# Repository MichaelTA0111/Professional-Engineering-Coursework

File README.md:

# Air Pollution Monitoring System
This is a repository for a free and open source air pollution monitoring system.

## Documentation
The documentation for this project is available in this repository as "APMS Documentation.pdf".

## Components
The system uses the following electronic components:
* Mbed NXP LPC1768
* Adafruit Monochrome 0.91” 128x32 I2C OLED Display
* RJ45 8-pin Connector
* SparkFun RJ45 Breakout
* RJ45 CAT6 Cable 5 m
* Adafruit BME680
* Thumb Joystick
* Thumb Joystick Breakout Board
* 5W Plug Adapter 5V DC
* DC Barrel Power Jack/Connector

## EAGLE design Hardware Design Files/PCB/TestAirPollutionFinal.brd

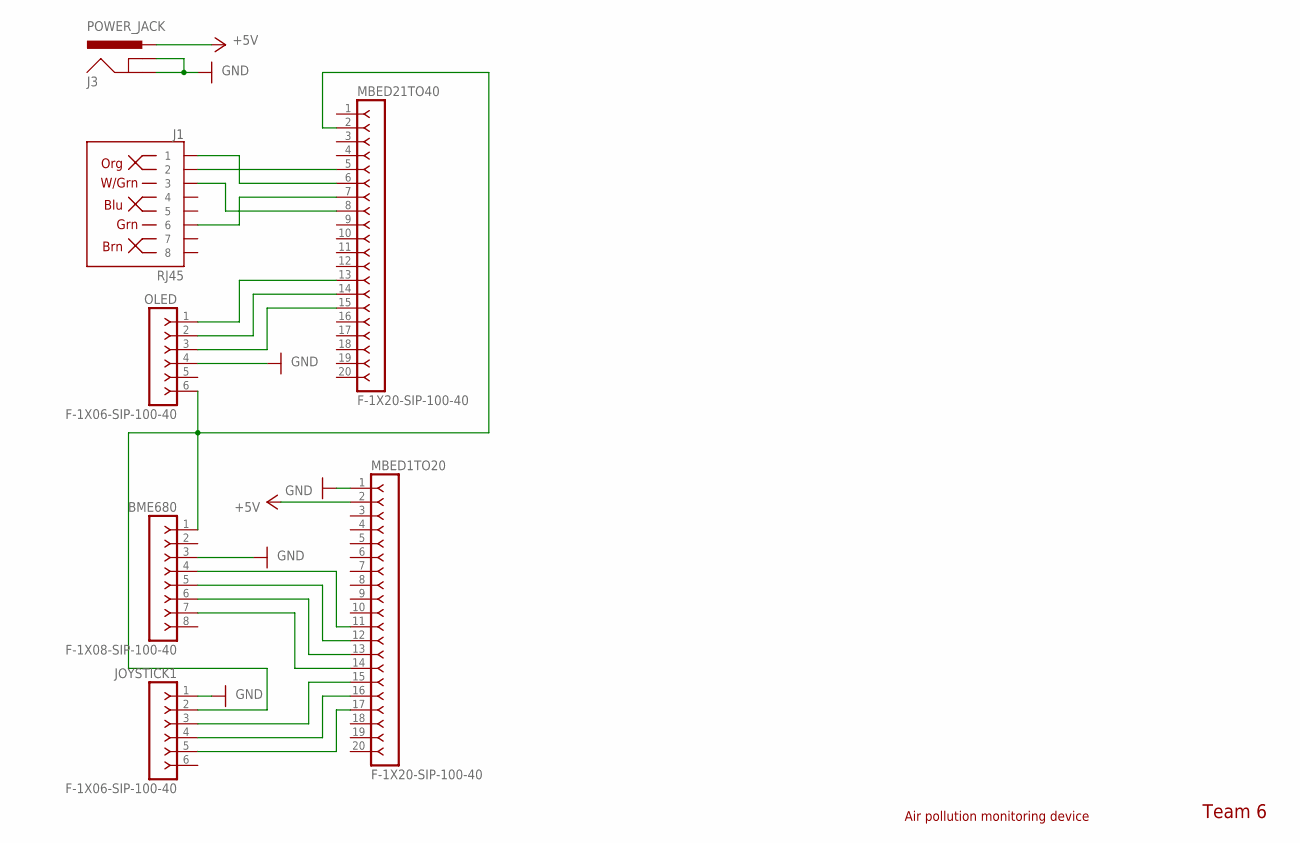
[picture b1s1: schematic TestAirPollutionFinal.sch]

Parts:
BME680: F-1X08-SIP-100-40; SIP-100-08-40
J1: RJ45; RJ45-8
J3: POWER_JACK; POWER_JACK_PTH
JOYSTICK1: F-1X06-SIP-100-40; SIP-100-06-40
MBED1TO20, MBED21TO40: F-1X20-SIP-100-40; SIP-100-20-40
OLED: F-1X06-SIP-100-40; SIP-100-06-40

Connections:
+5V: J3.PWR, MBED1TO20.2
CS: BME680.7, MBED1TO20.14
GND: BME680.3, J3.GND, J3.GNDBREAK, JOYSTICK1.1, MBED1TO20.1, OLED.4
RD+: J1.1, MBED21TO40.6
RD-: J1.2, MBED21TO40.5
RESET: MBED21TO40.15, OLED.3
SCK: BME680.4, MBED1TO20.11
SCLP27: MBED21TO40.14, OLED.2
SDAP28: MBED21TO40.13, OLED.1
SDI: BME680.6, MBED1TO20.13
SDO: BME680.5, MBED1TO20.12
SW: JOYSTICK1.5, MBED1TO20.17
TD+: J1.3, MBED21TO40.8
TD-: J1.6, MBED21TO40.7
VRX: JOYSTICK1.3, MBED1TO20.15
VRY: JOYSTICK1.4, MBED1TO20.16
VU: BME680.1, JOYSTICK1.2, MBED21TO40.2, OLED.6

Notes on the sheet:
Team 6
Air pollution monitoring device

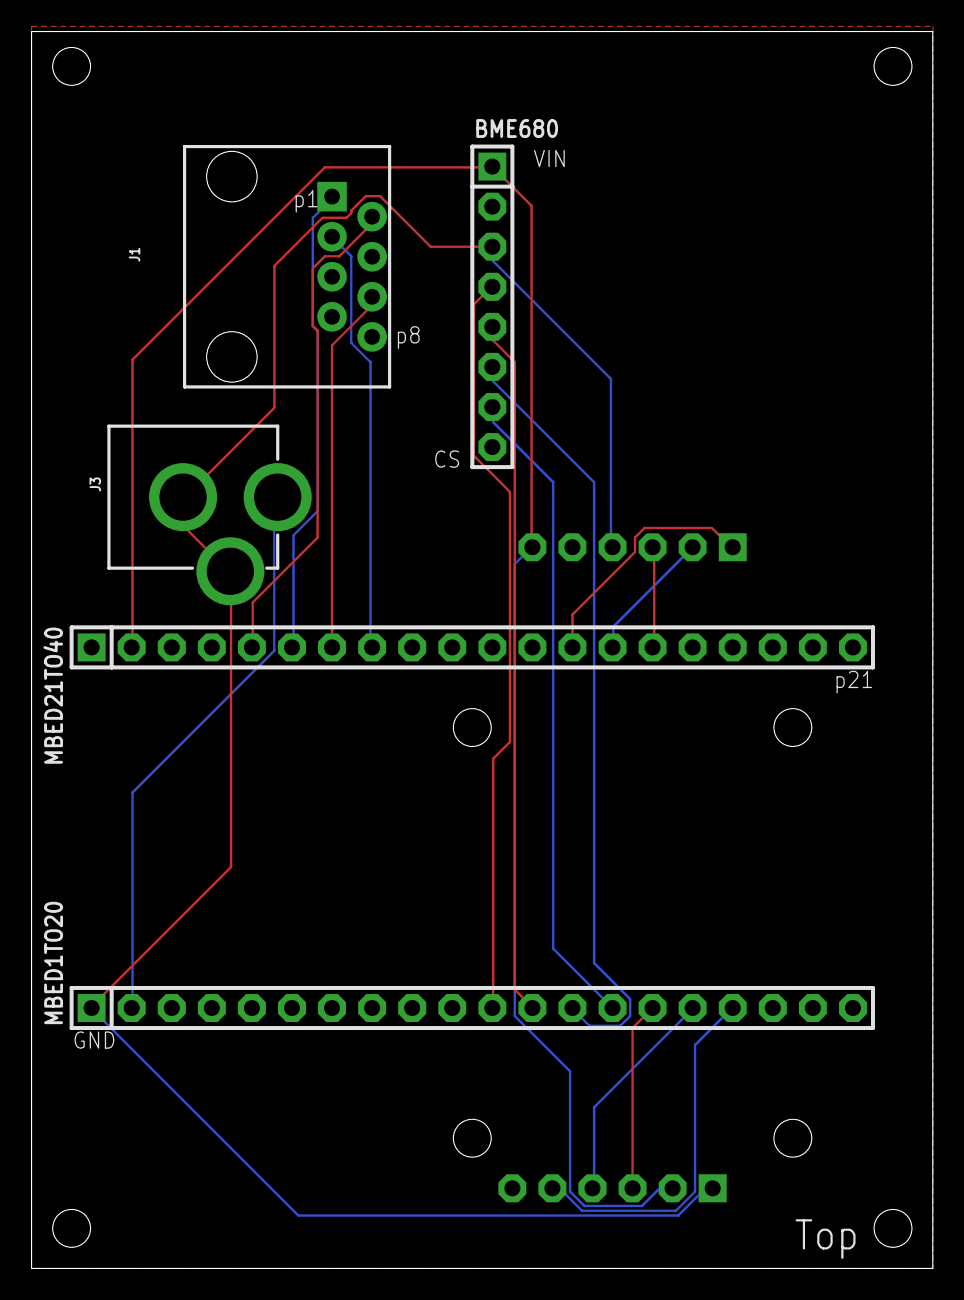
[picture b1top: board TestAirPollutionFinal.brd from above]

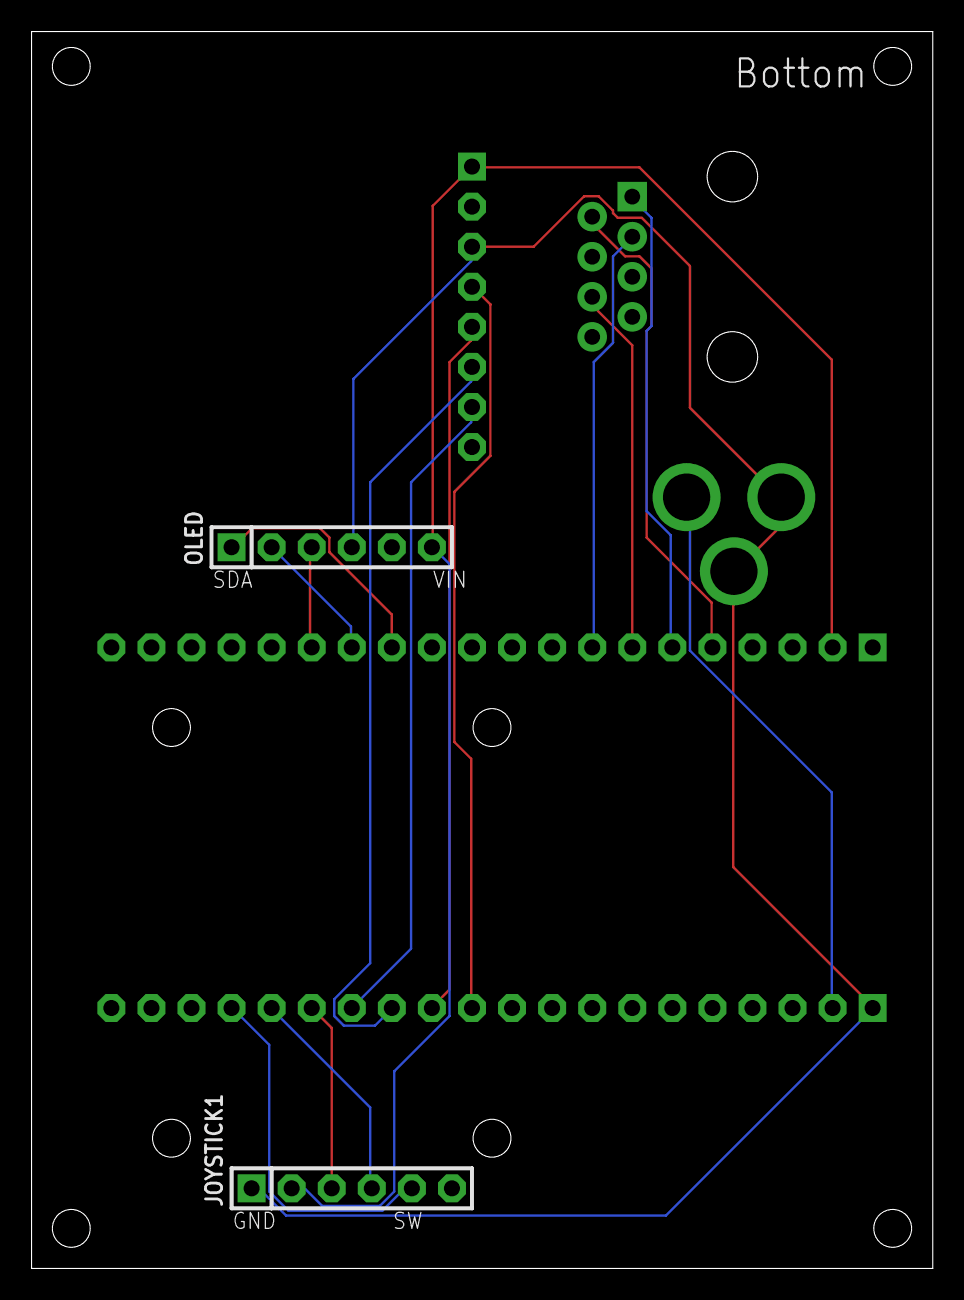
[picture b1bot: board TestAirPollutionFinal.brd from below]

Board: 2 copper layers, 57.1 x 78.4 mm, 7 parts (2 on the bottom side), 17 nets.

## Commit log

2021-01-21 Added link to attendance tracker
2021-01-22 Added CMake files to .gitignore
2021-01-22 Removed redundant definition
2021-01-23 Add mbed-os.lib
2021-01-23 Replace EventIntervalTrigger.h and EventIntervalTrigger.cpp with event-interval-trigger.lib
2021-01-27 Add LM75B.lib
2021-01-27 Correct comment in DatabaseManager.py
2021-02-02 Database can be read, graphs can be plotted
2021-02-06 Added statistics calculations to the data
2021-02-07 Fixed comments
2021-02-07 Added a method to convert a unix timestamp to a date string
2021-02-07 Added exporting data as a csv
2021-02-12 Slightly modified exporting to a csv to allow spaces in column headers
2021-02-12 Created a class for the sensors to inherit from
2021-02-12 Added watermarks to spite David Lim
2021-02-12 Added saving the graph to run.py
2021-02-13 Add default constructor to DataPackage.h and DataPackage.cpp
2021-02-13 Moved code from DataPackage.h to DataPackage.cpp
2021-02-15 Add PCB design files
2021-02-16 Redone comments
2021-02-16 Added a static method to parse a vector of data packets as a JSON
2021-02-16 Revert "Added a static method to parse a vector of data packets as a JSON"
    This reverts commit 7852cdb8
2021-02-16 Fixed spelling error in DataPackage.h
2021-02-16 Fix another spelling error in DataPackage.h
2021-02-21 Fix bug in method setStaticIpEnabled()
2021-02-22 Added check to member setIpAddress() to make sure network is disconnected
2021-02-26 Added the network handler class
2021-02-26 Added writing to the database
2021-02-26 Added examples of writing to the database
2021-03-29 Added checks to prevent connecting to ethernet once already connected
2021-03-29 Added default values for port and staticIp to NetworkHandler.h
2021-03-29 Add data receiving functionality to NetworkHandler.py
2021-04-07 Update mbed-os version
2021-04-07 Add default argument to timeout in constructor
2021-04-07 Add display library
2021-04-07 Disable splashscreen
2021-04-07 Add joystick.lib
2021-04-07 Add Menu
2021-04-07 Add sensor library
2021-04-09 Workaround bug in display library
2021-04-09 Update displayReadings() with correct readings to show
2021-04-09 Update use() with correct readings to show
2021-04-09 Revert "Update use() with correct readings to show"
    This reverts commit a491eb50
2021-04-09 Fix compiler warnings
2021-04-10 Reformat Menu.h and Menu.cpp
2021-04-10 Changed read behaviour in Sensor
2021-04-10 Update DataPackage to correct variable names
2021-04-10 Update to be compatible with new DataPackage
2021-04-10 Update Menu to use strings
2021-04-10 Add getIpAddress()
2021-04-10 Fix split_strings when input parameter is byte-like object
2021-04-10 Update field names and correct timestamps in insert method
2021-04-10 Change unix_time from milliseconds to seconds
2021-04-11 Bug fix in NetworkHandler.cpp
2021-04-11 Implement network connectivity
2021-04-11 Create compiled binary file for the microcontroller
2021-04-11 Update db_read() with correct table collumns
2021-04-12 Add error messages to exceptions
2021-04-13 Add return types to getters
2021-04-13 Remove commented code
2021-04-13 Create NewJoystick
2021-04-13 Reformat NewJoystick
2021-04-13 Add default return to direction_pressed()
2021-04-13 Reorder NewJoystick constructor
2021-04-13 Add comments
2021-04-13 Correct parameters
2021-04-14 Add files via upload
    Just an update with the new test data displayed appropriately on the graphs, the main menu still needs to be tweaked.
2021-04-14 Correct graphs and labels and some tidying in progress
2021-04-14 Completed the graph_init implimentation.
    Next stage is to add the time range input and button to update graphs.
2021-04-21 New headings
    The majority is completed however the time range entered has to be in unix (currently uses default data) and the exporter simply exports to 'statistics .csv'.
2021-04-21 Some minor tweaks.
    Corrected the main menu and when the graphs are updated the grid is plotted and labels are correct.
2021-04-22 Add enclosure design file
2021-04-23 Add pdf of documentation
2021-04-24 Create LICENSE

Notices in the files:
parts and their libraries:
con-headers-jp: Copyright (C) 2008, Bob Starr
SparkFun-Connectors: Licensing: Creative Commons ShareAlike 4.0 International - https://creativecommons.org/licenses/by-sa/4.0
